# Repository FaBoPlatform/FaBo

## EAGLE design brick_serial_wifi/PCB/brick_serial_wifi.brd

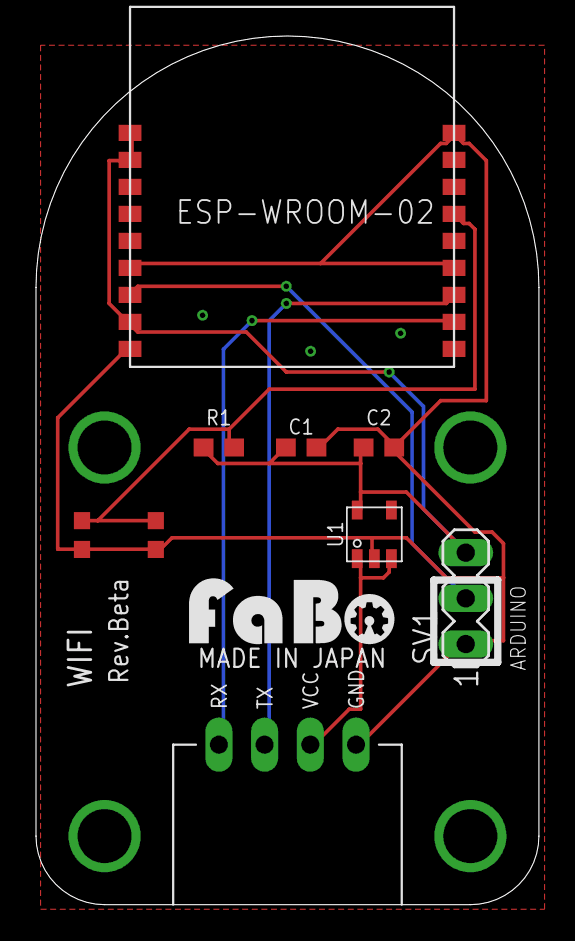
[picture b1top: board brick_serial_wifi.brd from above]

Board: 2 copper layers, 27.9 x 48.3 mm, 10 parts (0 on the bottom side), 7 nets.

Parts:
C1: 1uF; EIA0603
C2: 0.1uf; EIA0603
J1: FABO_BRICK_SERIAL_LONG
R1: 4.7k; EIA0603
SV1: MA03-1
U1: SOT_23_5
U$1: ES-ESPWROOM02
U$3: LOGO_FABO_M
U$4: LOGO_OSHW_T_M_BOTTOM
U$7: SWICTH-4P(KMR2); SWITCH-4P(KMR2)

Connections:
3V3: C1.1, C2.1, R1.1, SV1.3, U1.5, U$1.1, U$1.2, U$1.8
GND: C1.2, C2.2, J1.GND, SV1.1, U1.2, U$1.6, U$1.9, U$1.13, U$1.18, U$7.3, U$7.4
IO2: SV1.2, U$1.7
unnamed: J1.VCC, U1.1, U1.3
RESET: R1.2, U$1.15, U$7.1, U$7.2
RX: J1.RX, U$1.11
TX: J1.TX, U$1.12

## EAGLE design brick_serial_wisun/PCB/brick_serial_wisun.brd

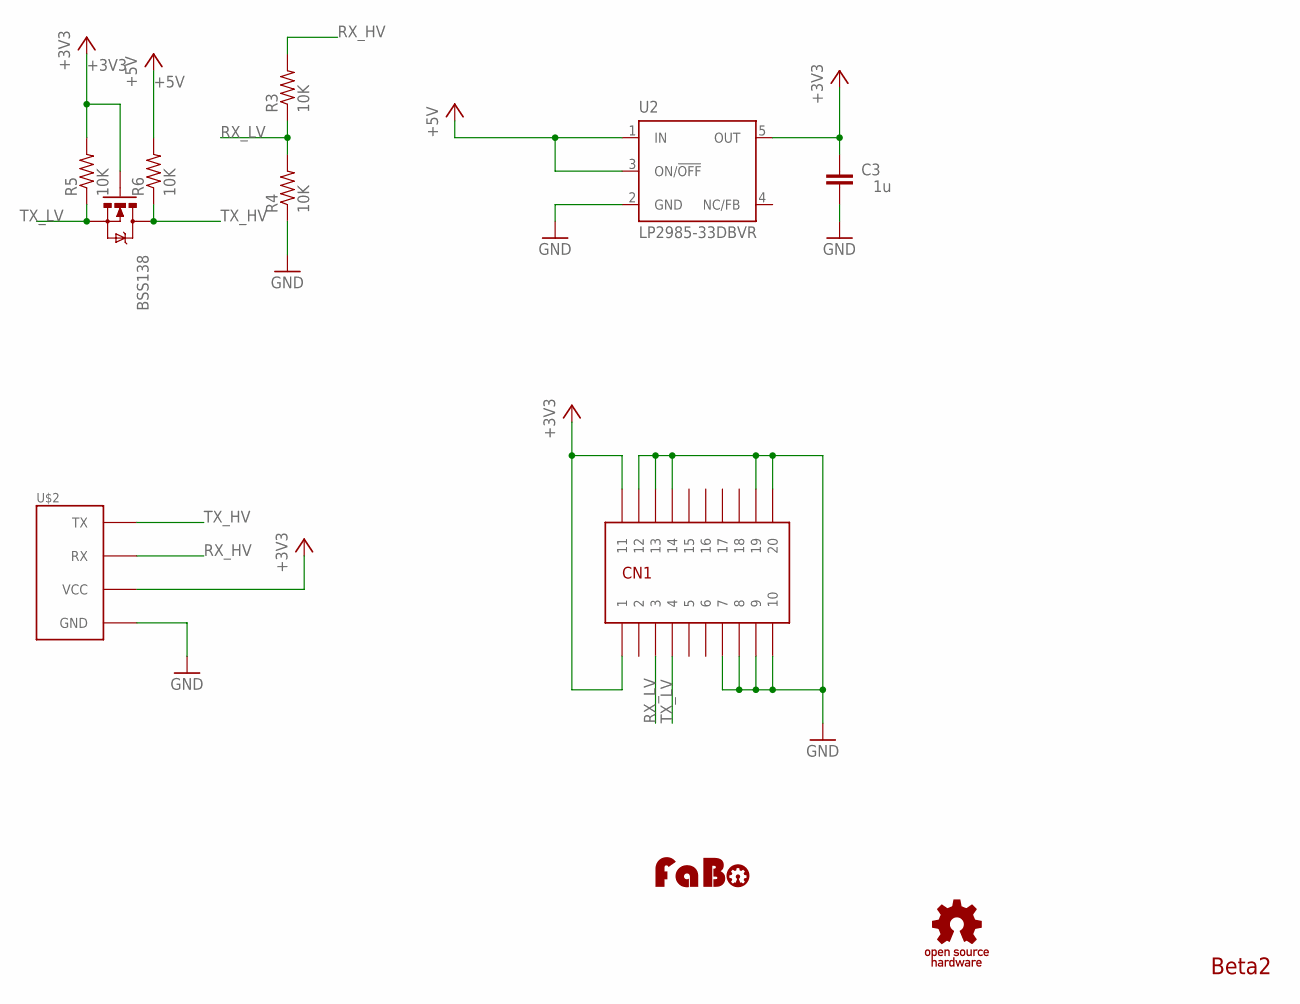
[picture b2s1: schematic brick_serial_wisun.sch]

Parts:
BSS138: MOSFET-NCHANNELSMD; SOT23-3
C3: 1u; C0603-ROUND
CN1: JST-20P3.0-JMCS
R3, R4, R5, R6: 10K; 0603-RES
U2: LP2985-33DBVR; SOT23-DBV
U$1: LOGO_OSHW_T-S; LOGO_OSHW_T_S
U$2: BRICK_SERIAL
U$4: LOGO_FABO-S; LOGO_FABO_S

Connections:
+3V3: BSS138.1 (G), C3.2, CN1.10 (1), CN1.20 (11), R5.2, U2.5 (OUT), U$2.VCC
+5V: R6.2, U2.1 (IN), U2.3 (ON/!OFF)
GND: C3.1, CN1.1 (10), CN1.2 (9), CN1.3 (8), CN1.4 (7), CN1.11 (20), CN1.12 (19), CN1.17 (14), CN1.18 (13), CN1.19 (12), R4.1, U2.2 (GND), U$2.GND
RX_HV: R3.2, U$2.RX
RX_LV: CN1.8 (3), R3.1, R4.2
TX_HV: BSS138.3 (D), R6.1, U$2.TX
TX_LV: BSS138.2 (S), CN1.7 (4), R5.1

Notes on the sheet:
Beta2

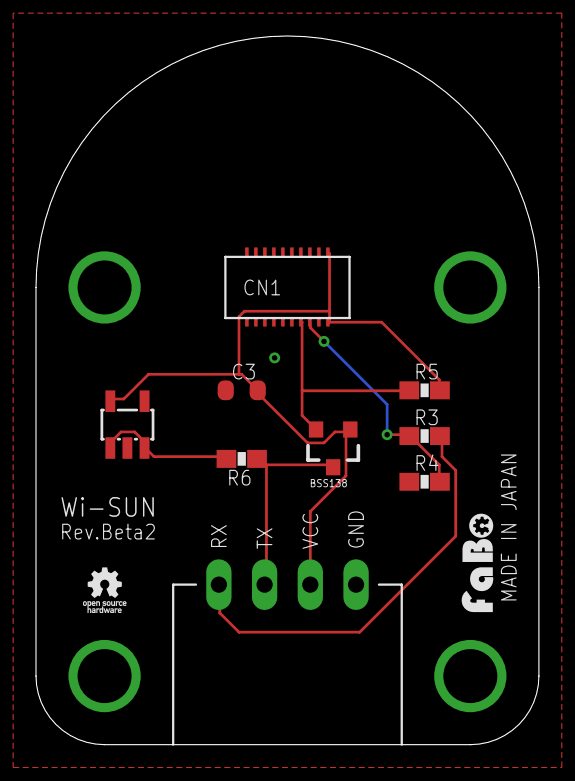
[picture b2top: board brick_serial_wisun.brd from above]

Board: 2 copper layers, 27.9 x 39.4 mm, 11 parts (0 on the bottom side), 7 nets.

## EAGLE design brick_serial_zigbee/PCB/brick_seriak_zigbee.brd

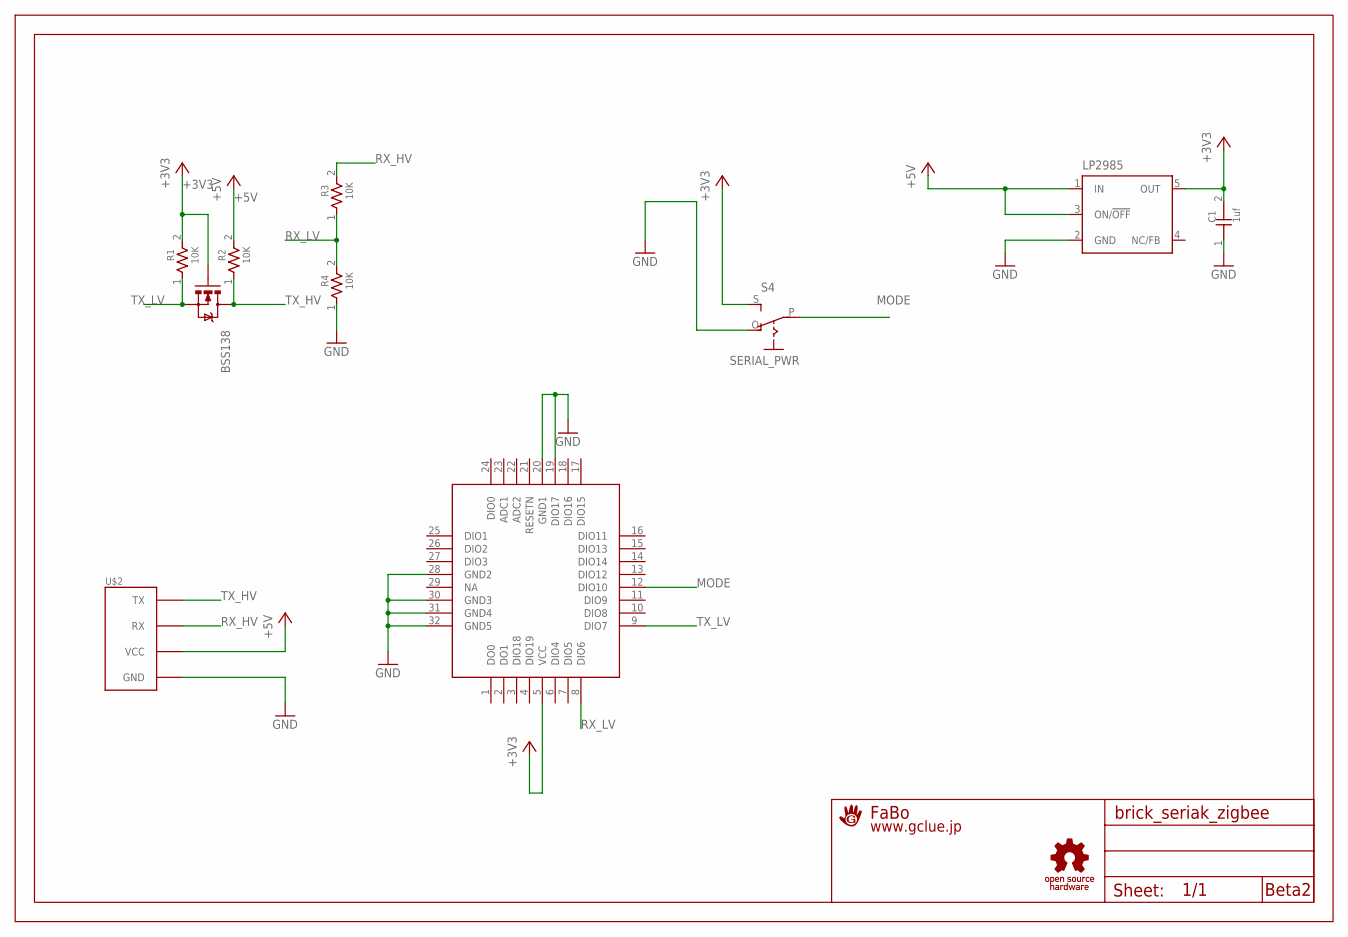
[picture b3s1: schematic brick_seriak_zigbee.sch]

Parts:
BSS138: MOSFET-NCHANNELSMD; SOT23-3
C1: 1uf; 0603
LP2985: LP2985-XXDBVR33; SOT23-DBV
R1, R2, R3, R4: 10K; 0603
S4: SERIAL_PWR; EG1218
U$1: A4L-LOC-FABO_S; LOGO_FABO_S
U$2: BRICK_SERIAL
U$3: TOCOS-TWE001L
U$5: LOGO_OSHW_T-S; LOGO_OSHW_T_S

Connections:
+3V3: BSS138.1 (G), C1.2, LP2985.5 (OUT), R1.2, S4.S, U$3.5 (VCC)
+5V: LP2985.1 (IN), LP2985.3 (ON/!OFF), R2.2, U$2.VCC
GND: C1.1, LP2985.2 (GND), R4.1, S4.O, U$2.GND, U$3.19 (DIO17), U$3.20 (GND1), U$3.28 (GND2), U$3.30 (GND3), U$3.31 (GND4), U$3.32 (GND5)
MODE: S4.P, U$3.12 (DIO10)
RX_HV: R3.2, U$2.RX
RX_LV: R3.1, R4.2, U$3.8 (DIO6)
TX_HV: BSS138.3 (D), R2.1, U$2.TX
TX_LV: BSS138.2 (S), R1.1, U$3.9 (DIO7)

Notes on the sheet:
Beta2

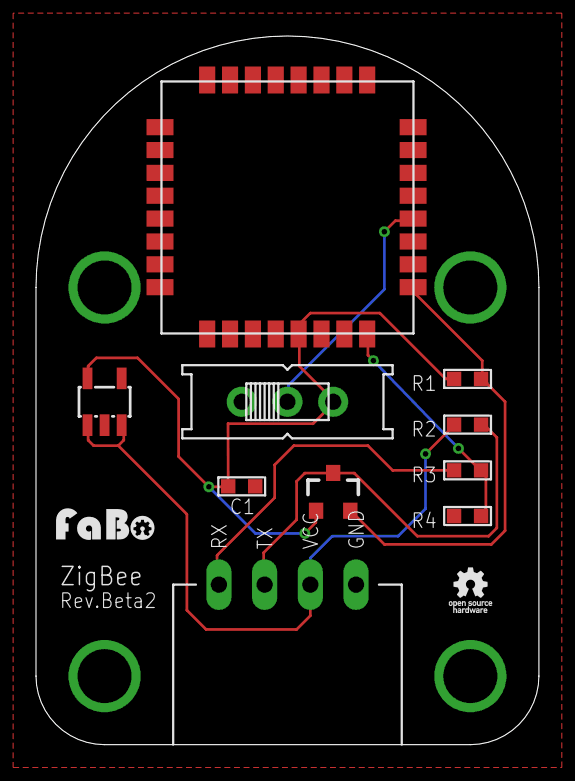
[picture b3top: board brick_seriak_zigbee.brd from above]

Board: 2 copper layers, 27.9 x 39.4 mm, 12 parts (0 on the bottom side), 8 nets.

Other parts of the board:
U$4: LOGO_FABO_S

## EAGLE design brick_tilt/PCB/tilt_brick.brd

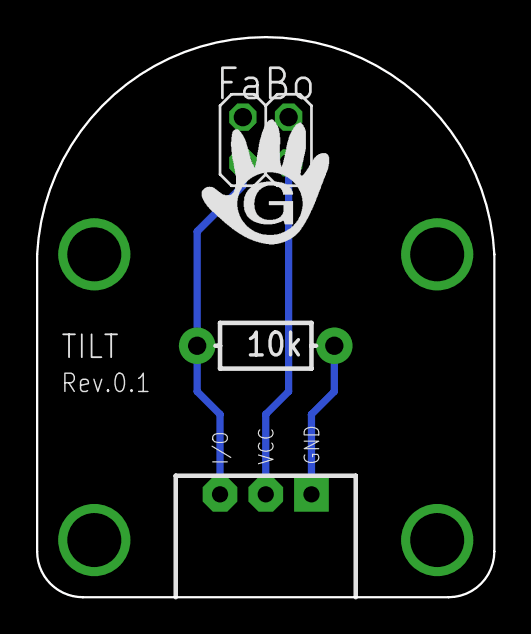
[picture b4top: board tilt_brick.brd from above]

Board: 2 copper layers, 25.4 x 31.1 mm, 3 parts (0 on the bottom side), 3 nets.

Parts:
J1: BRICK_3PIN
R1: 10k; AXIAL-0.3-KIT
U1: TILT; 2X02

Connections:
GND: J1.GND, R1.P$1
unnamed: J1.IN/OUT, R1.P$2, U1.1
unnamed: J1.VCC, U1.3

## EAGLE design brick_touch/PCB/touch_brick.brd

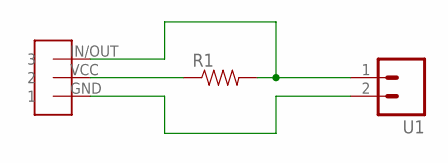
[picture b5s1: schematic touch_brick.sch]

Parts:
R1: RESISTORKIT; AXIAL-0.3-KIT
U1: M02LOCK; 1X02_LOCK
U$1: BRICK-3PIN; BRICK_3PIN

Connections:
GND: U1.2, U$1.GND (1)
unnamed: R1.P$2 (2), U1.1, U$1.IN/OUT (3)
unnamed: R1.P$1 (1), U$1.VCC (2)

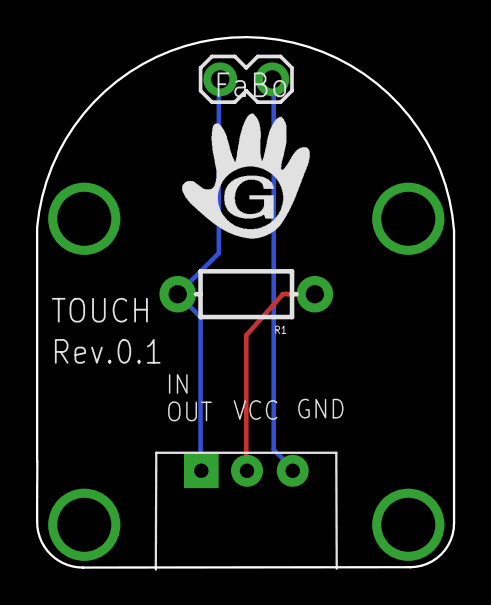
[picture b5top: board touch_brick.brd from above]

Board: 2 copper layers, 23.2 x 29.5 mm, 3 parts (0 on the bottom side), 3 nets.

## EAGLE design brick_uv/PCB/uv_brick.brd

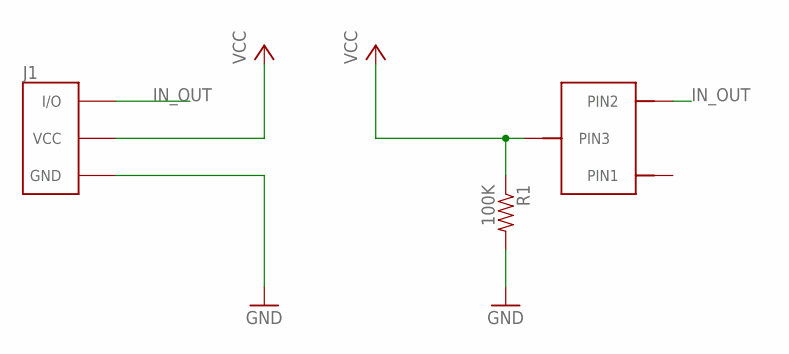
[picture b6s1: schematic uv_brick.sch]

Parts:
J1: BRICK_3PIN
R1: 100K; 0603-RES
U$1: GAASP-G6262

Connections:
GND: J1.GND, R1.2
IN_OUT: J1.IN/OUT (I/O), U$1.2 (PIN2)
VCC: J1.VCC, R1.1, U$1.3 (PIN3)

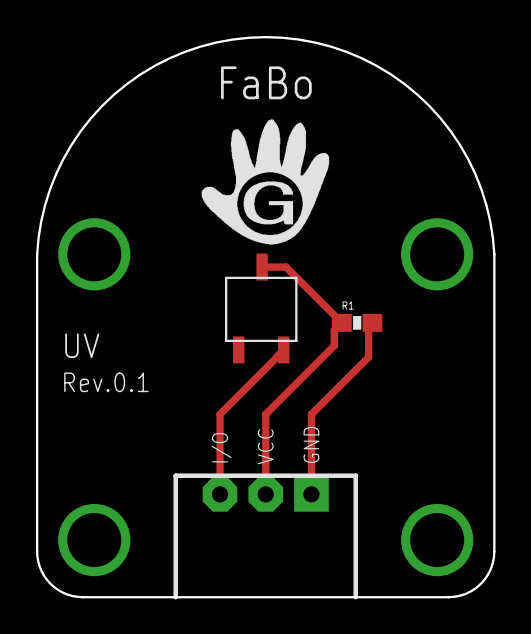
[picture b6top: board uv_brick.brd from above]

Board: 2 copper layers, 25.4 x 31.1 mm, 3 parts (0 on the bottom side), 3 nets.

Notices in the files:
parts and their libraries:
FaBo-etc: Released under the Creative Commons Attribution-ShareAlike 4.0 License
https://creativecommons.org/licenses/by-sa/4.0
SparkFun: Licensing: CC v3.0 Share-Alike You are welcome to use this library for commercial purposes.
